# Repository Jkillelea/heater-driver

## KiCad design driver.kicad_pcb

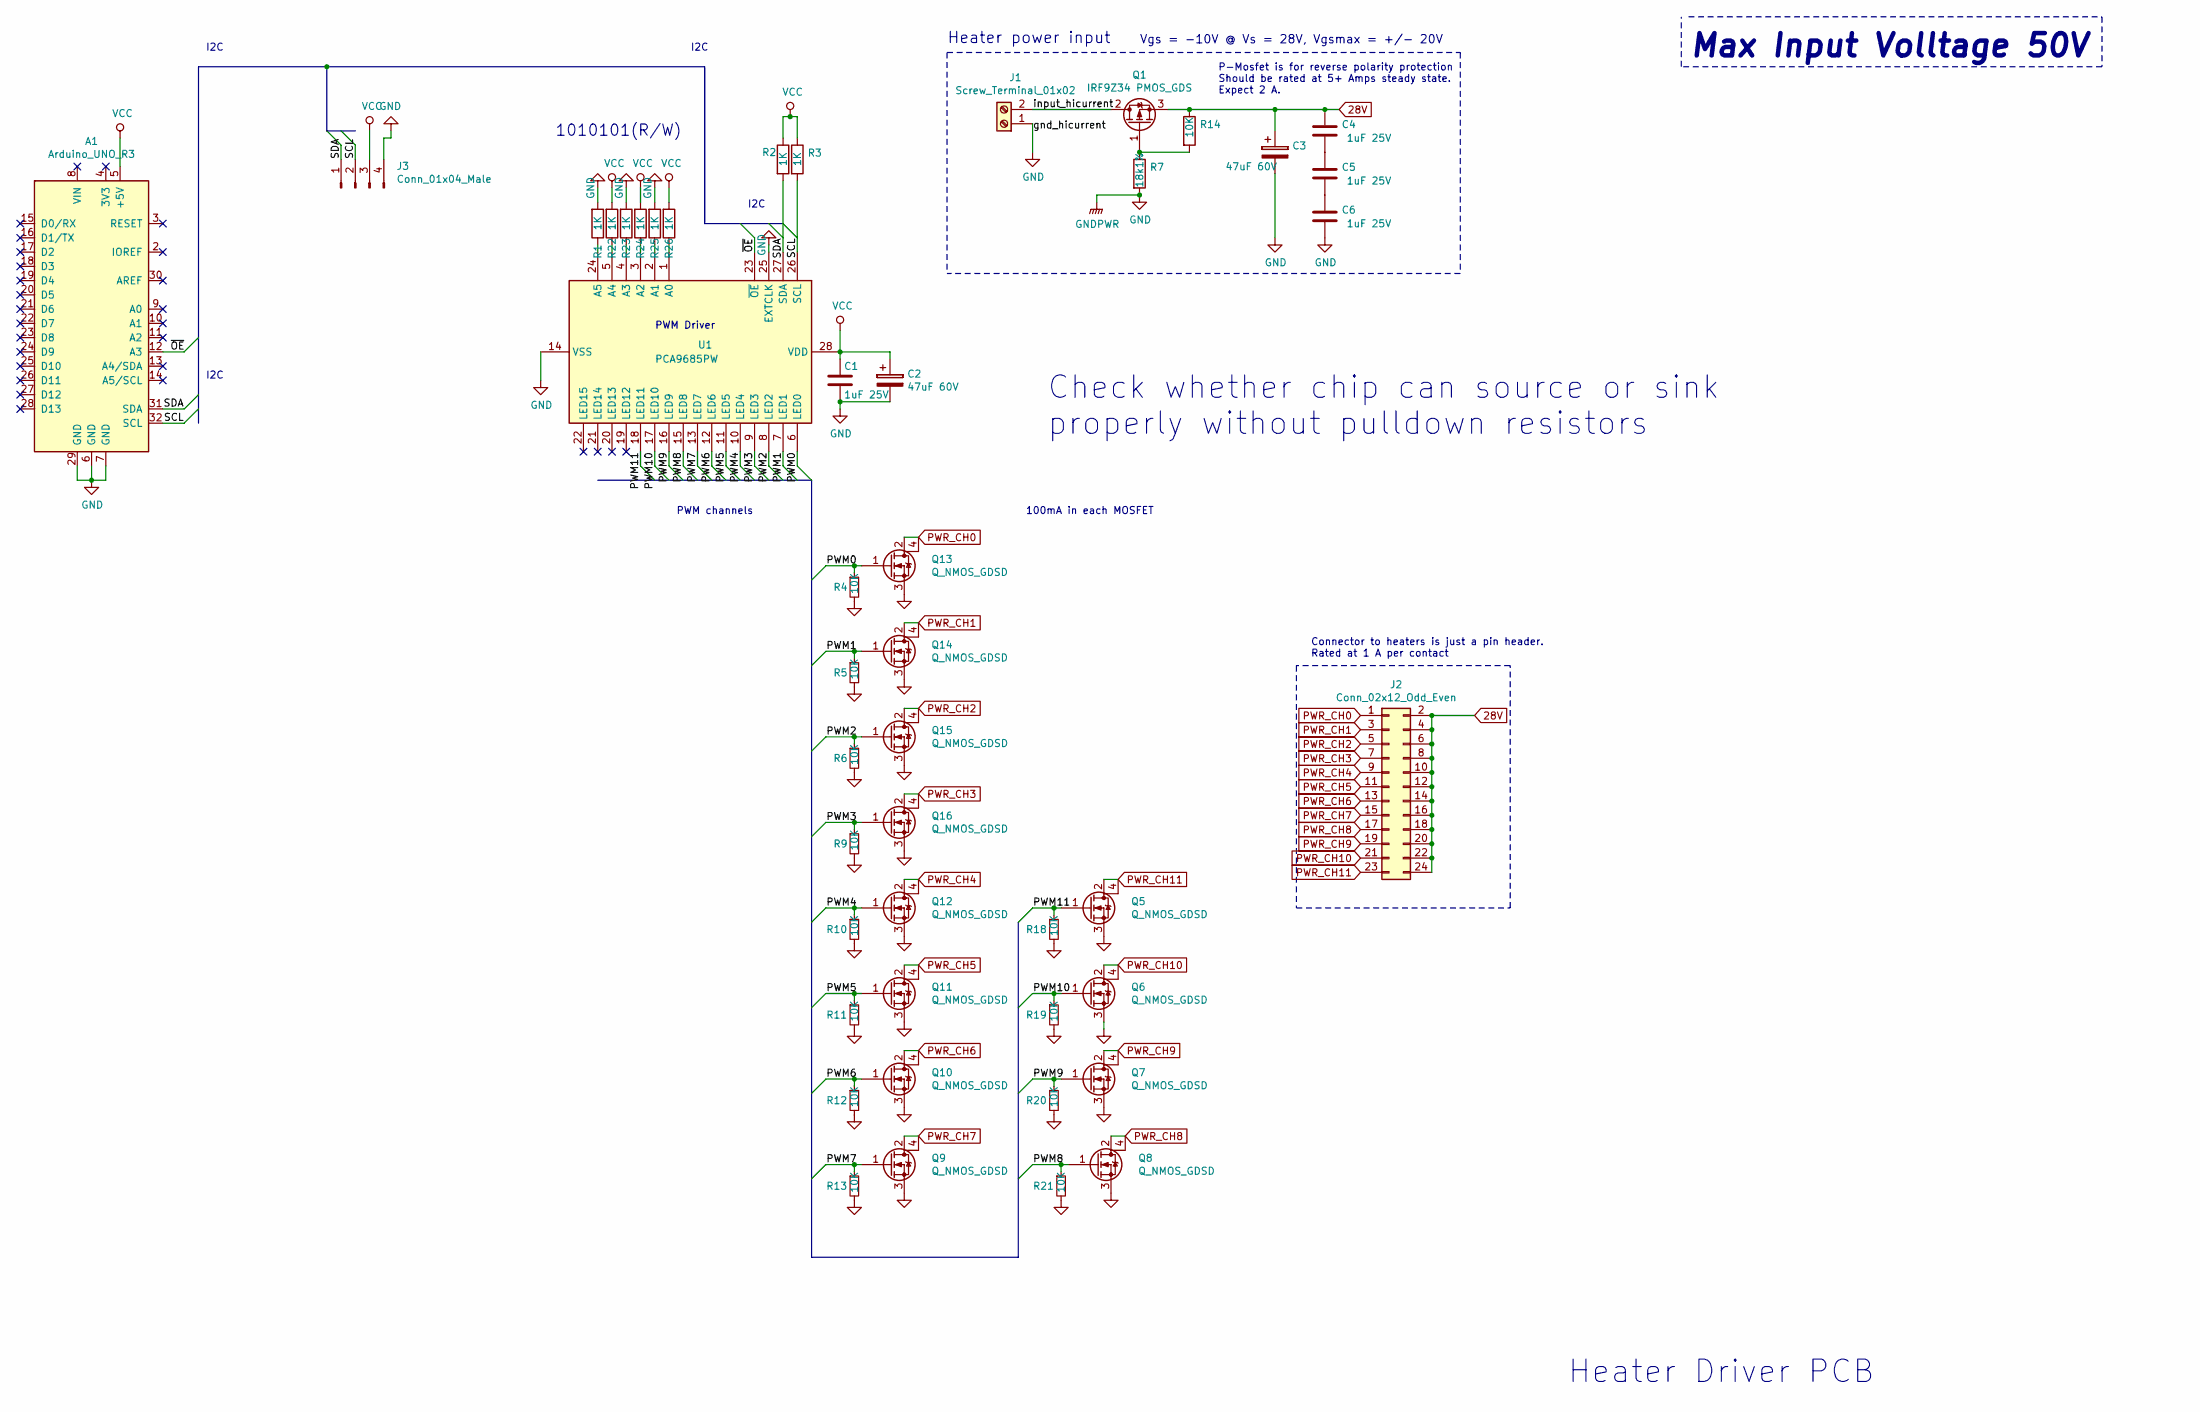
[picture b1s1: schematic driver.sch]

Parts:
A1: Arduino_UNO_R3
C1, C4, C5, C6: 1uF 25V; C_1206_3216Metric_Pad1.42x1.75mm_HandSolder
C2, C3: 47uF 60V; CP_Radial_D6.3mm_P2.50mm
J1: Screw_Terminal_01x02; TerminalBlock_MetzConnect_Type055_RT01502HDWU_1x02_P5.00mm_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
J2: Conn_02x12_Odd_Even; PinHeader_2x12_P2.54mm_Vertical
J3: Conn_01x04_Male; PinHeader_1x04_P1.27mm_Vertical
Q1: IRF9Z34 PMOS_GDS; TO-220-3_Vertical
Q5, Q6, Q7, Q8, Q9, Q10, Q11, Q12, Q13, Q14, Q15, Q16: Q_NMOS_GDSD; SOT-223
R1, R2, R3, R22, R23, R24, R25, R26: 1K; R_0805_2012Metric_Pad1.15x1.40mm_HandSolder
R4, R5, R6, R9, R10, R11, R12, R13, R14, R18, R19, R20, R21: 10K; R_1206_3216Metric_Pad1.42x1.75mm_HandSolder
R7: 18k1%; R_1206_3216Metric_Pad1.42x1.75mm_HandSolder
U1: PCA9685PW; TSSOP-28_4.4x9.7mm_P0.65mm

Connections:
28V: C3.1, C4.1, J2.2, J2.4, J2.6, J2.8, J2.10, J2.12, J2.14, J2.16, J2.18, J2.20, J2.22, J2.24, Q1.3 (S), R14.1
/PWM0: Q13.1 (G), R4.1, U1.6 (LED0)
/PWM1: Q14.1 (G), R5.1, U1.7 (LED1)
/PWM2: Q15.1 (G), R6.1, U1.8 (LED2)
/PWM3: Q16.1 (G), R9.1, U1.9 (LED3)
/PWM4: Q12.1 (G), R10.1, U1.10 (LED4)
/PWM5: Q11.1 (G), R11.1, U1.11 (LED5)
/PWM6: Q10.1 (G), R12.1, U1.12 (LED6)
/PWM7: Q9.1 (G), R13.1, U1.13 (LED7)
/PWM8: Q8.1 (G), R21.1, U1.15 (LED8)
/PWM9: Q7.1 (G), R20.1, U1.16 (LED9)
/PWM10: Q6.1 (G), R19.1, U1.17 (LED10)
/PWM11: Q5.1 (G), R18.1, U1.18 (LED11)
/SCL: A1.32 (SCL), J3.2, R3.2, U1.26 (SCL)
/SDA: A1.31 (SDA), J3.1, R2.2, U1.27 (SDA)
/input_hicurrent: J1.2, Q1.2 (D)
/~OE: A1.12 (A3), U1.23 (~OE)
GND: A1.6 (GND), A1.7 (GND), A1.29 (GND), C1.2, C2.2, C3.2, C6.2, J1.1, J3.4, Q5.3 (S), Q6.3 (S), Q7.3 (S), Q8.3 (S), Q9.3 (S), Q10.3 (S), Q11.3 (S), Q12.3 (S), Q13.3 (S), Q14.3 (S), Q15.3 (S), Q16.3 (S), R1.2, R4.2, R5.2, R6.2, R7.2, R9.2, R10.2, R11.2, R12.2, R13.2, R18.2, R19.2, R20.2, R21.2, R23.2, R25.2, U1.14 (VSS), U1.25 (EXTCLK)
unnamed: C4.2, C5.1
unnamed: C5.2, C6.1
unnamed: Q1.1 (G), R7.1, R14.2
unnamed: R1.1, U1.24 (A5)
unnamed: R22.1, U1.5 (A4)
unnamed: R23.1, U1.4 (A3)
unnamed: R24.1, U1.3 (A2)
unnamed: R25.1, U1.2 (A1)
unnamed: R26.1, U1.1 (A0)
PWR_CH0: J2.1, Q13.2 (D), Q13.4 (D)
PWR_CH1: J2.3, Q14.2 (D), Q14.4 (D)
PWR_CH2: J2.5, Q15.2 (D), Q15.4 (D)
PWR_CH3: J2.7, Q16.2 (D), Q16.4 (D)
PWR_CH4: J2.9, Q12.2 (D), Q12.4 (D)
PWR_CH5: J2.11, Q11.2 (D), Q11.4 (D)
PWR_CH6: J2.13, Q10.2 (D), Q10.4 (D)
PWR_CH7: J2.15, Q9.2 (D), Q9.4 (D)
PWR_CH8: J2.17, Q8.2 (D), Q8.4 (D)
PWR_CH9: J2.19, Q7.2 (D), Q7.4 (D)
PWR_CH10: J2.21, Q6.2 (D), Q6.4 (D)
PWR_CH11: J2.23, Q5.2 (D), Q5.4 (D)
VCC: A1.5 (+5V), C1.1, C2.1, J3.3, R2.1, R3.1, R22.2, R24.2, R26.2, U1.28 (VDD)

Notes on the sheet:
Heater power input
PWM Driver
P-Mosfet is for reverse polarity protection Should be rated at 5+ Amps steady state. Expect 2 A.
I2C
PWM channels
100mA in each MOSFET
Connector to heaters is just a pin header. Rated at 1 A per contact
Heater Driver PCB
Check whether chip can source or sink properly without pulldown resistors
1010101(R/W)
Vgs = -10V @ Vs = 28V, Vgsmax = +/- 20V
Max Input Volltage 50V

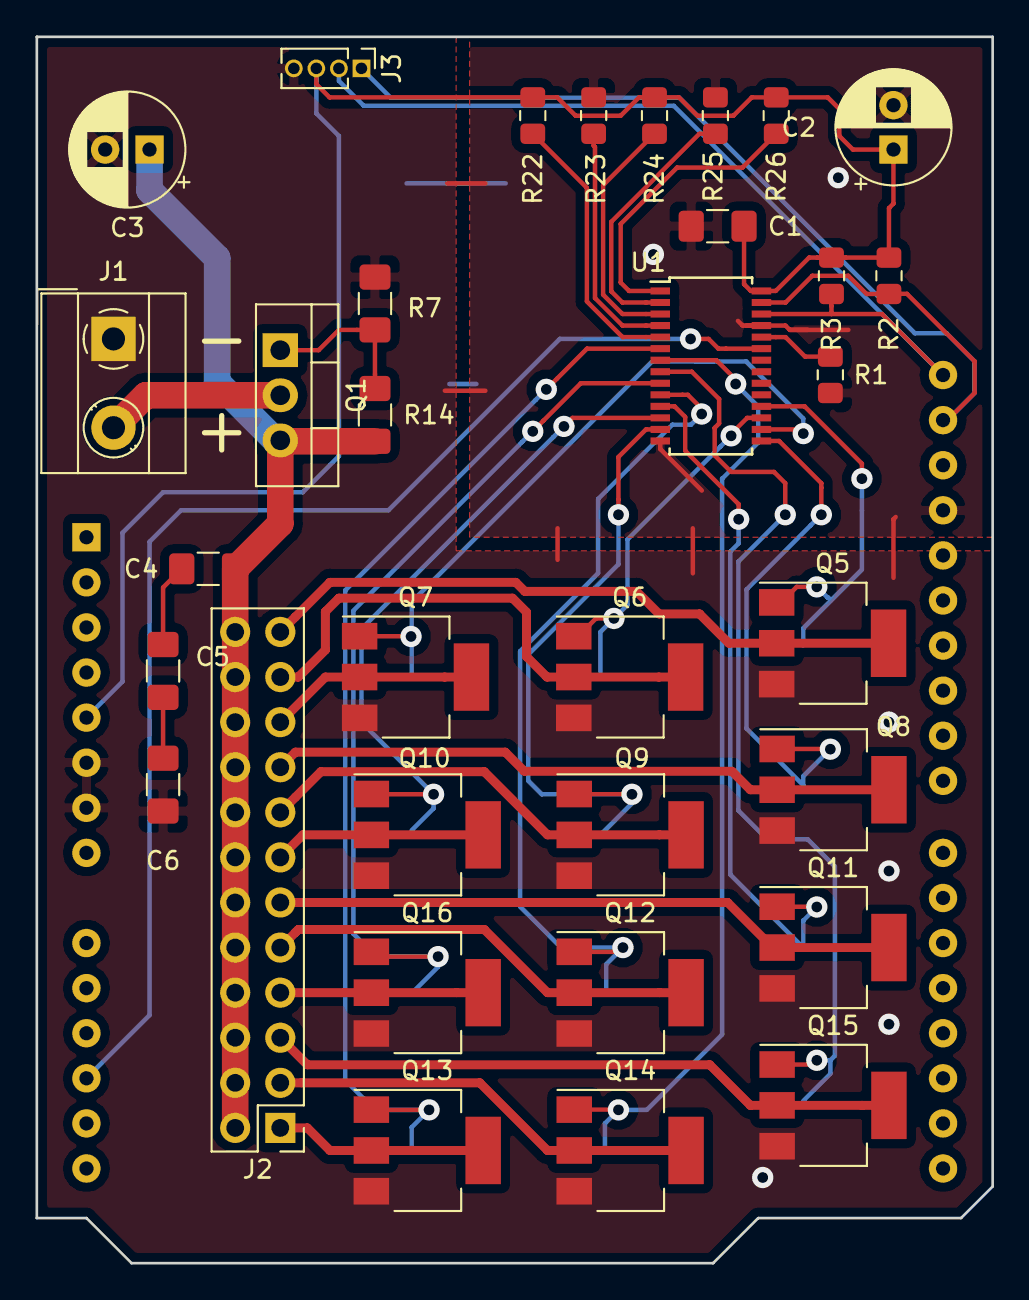
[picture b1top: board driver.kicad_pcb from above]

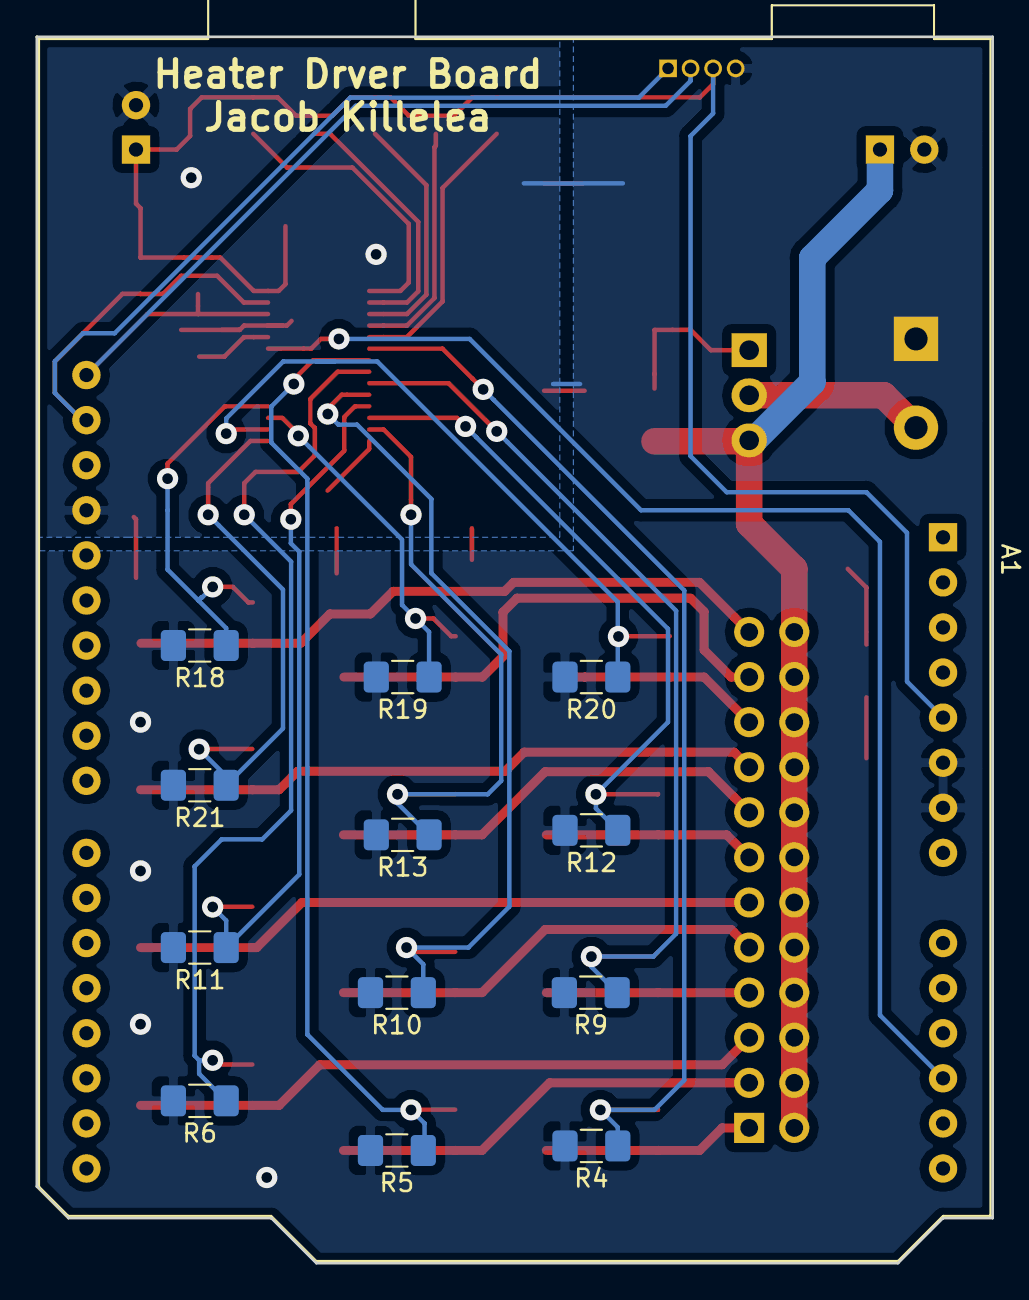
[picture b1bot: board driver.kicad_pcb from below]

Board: 2 copper layers, 53.8 x 69.1 mm, 46 parts (13 on the bottom side), 40 nets.

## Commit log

2019-01-18 first
2019-01-19 28V heater power input, reverse polarity protection, early BOM
2019-01-19 connector selected, beginning routing
2019-01-22 reroute schematic + component placement
2019-01-26 Trudy's notes
2019-01-26 add pulldown resistors
2019-01-26 ground extclk as per datasheet
2019-01-26 change address
2019-01-27 Change all resistors to 10K 0805. More routing and placement
2019-01-28 remove capacitor footprints and organize.
2019-01-28 replace zener with voltage divdier, swap MOSFETs, update footprints, separate power and signal ground planes
2019-01-30 Capacitor updates + voltage limit 50V + routing
2019-01-30 Remove reset button, finalize capacitor sizes
2019-01-30 resistor value/footprint changes and associated routing changes
2019-01-30 routing and placement
2019-01-31 misc routing updates
2019-01-31 polarity markings on terminal block, routing
2019-02-01 As sent to jlcpcb
2019-02-06 update for mosfet pinout change
2019-02-08 ITLL design rule tolerances and sizes, neccesistated a full re-routing of all traces
2019-04-23 final version, sending to GA
